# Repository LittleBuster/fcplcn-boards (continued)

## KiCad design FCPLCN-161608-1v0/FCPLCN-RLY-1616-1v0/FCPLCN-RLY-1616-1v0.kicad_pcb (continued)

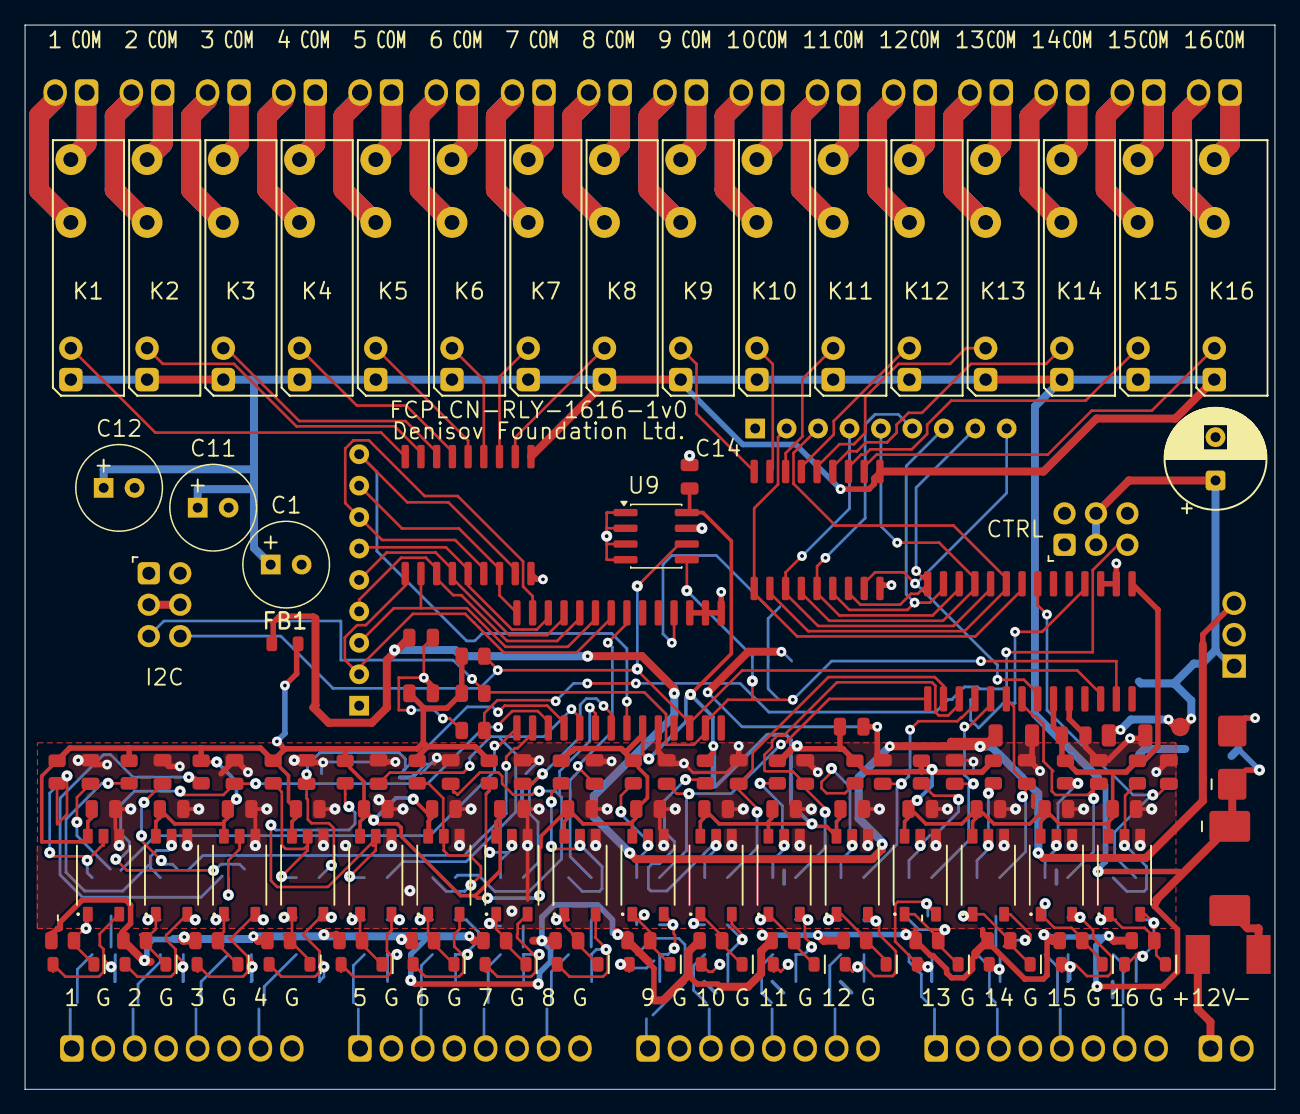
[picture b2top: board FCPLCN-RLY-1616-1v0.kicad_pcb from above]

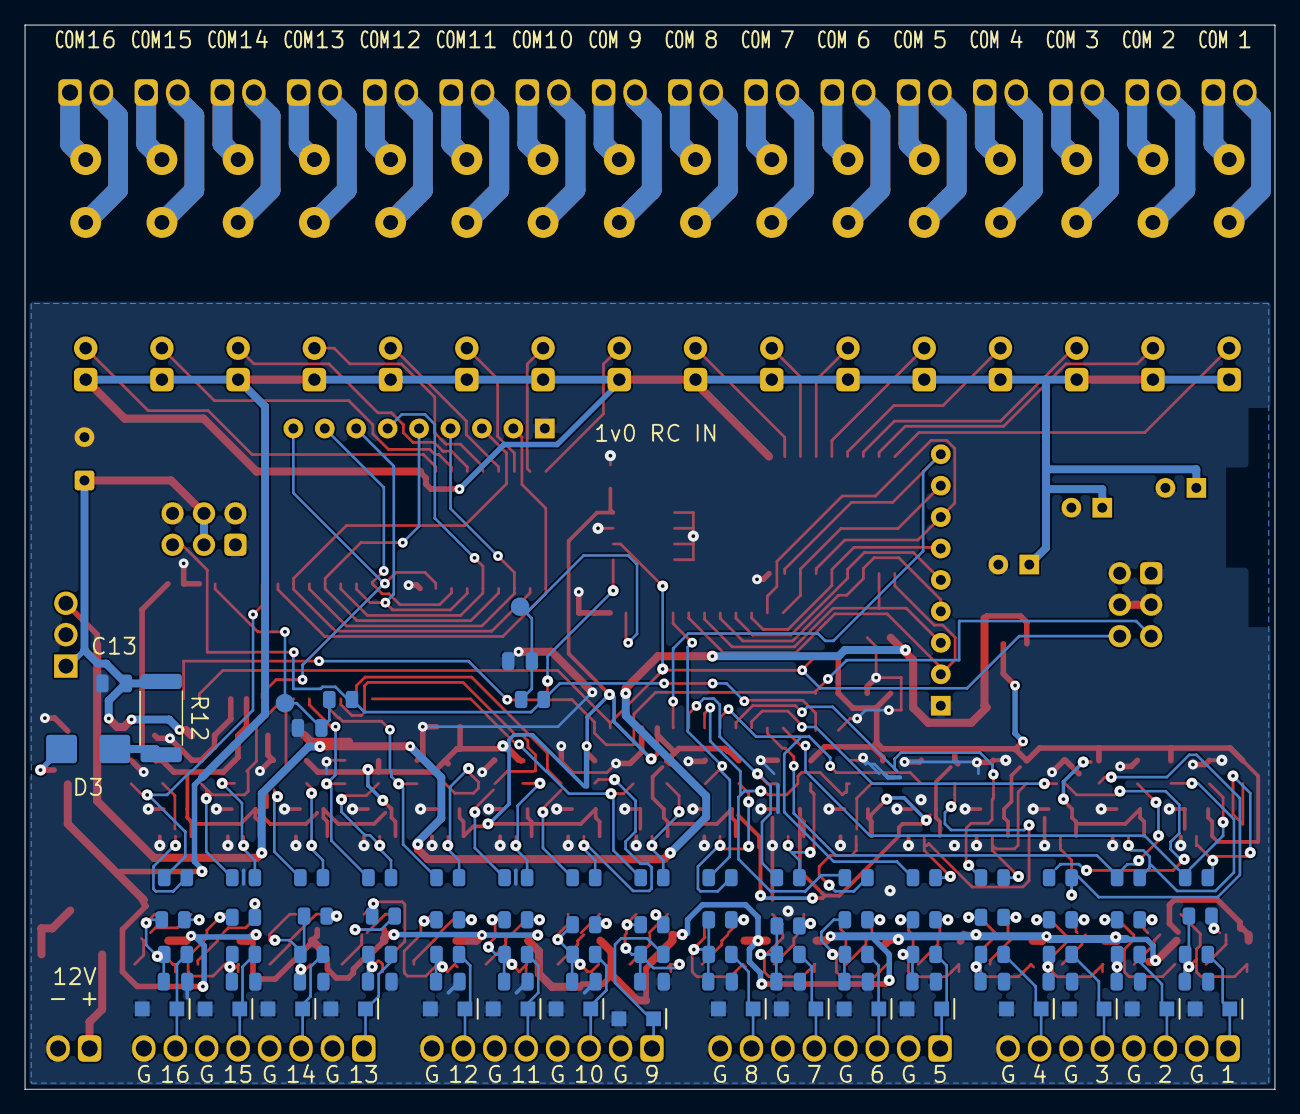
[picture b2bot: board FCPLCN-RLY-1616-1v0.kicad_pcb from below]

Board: 2 copper layers, 101.0 x 86.0 mm, 251 parts (89 on the bottom side), 157 nets.

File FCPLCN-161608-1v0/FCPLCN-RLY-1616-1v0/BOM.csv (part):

refs,value,footprint,qty,datasheet,mpn,manufacturer,tolerance,supplier_part_number,source_url,package,bom_group,power_rating,voltage,dielectric,resistor_type,height_max,cad_footprints
"C1, C11, C12",100u / 35V,RelayBoard:CP_APAQ_ARHA_D6.3mm_P2.5mm_H9max,3,https://www.apaq.com.tw/Templates/att/ARHA_20241121.pdf?lng=en,350ARHA101M06X8P00,APAQ,20%,C217555,https://www.lcsc.com/product-detail/C217555.html,RelayBoard:CP_APAQ_ARHA_D6.3mm_P2.5mm_H9max,,,,,,9 mm,RelayBoard:CP_APAQ_ARHA_D6.3mm_P2.5mm_H9max
"C2, C3",10uF,RelayBoard:C_1206_3216Metric,2,https://product.tdk.com/system/files/dam/doc/product/capacit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,C3216X7R1V106K160AC,TDK,10%,,,1206,C-1206-10uF-35V-X7R-10pct-TDK,,35 V,X7R,,1.8 mm,RelayBoard:C_1206_3216Metric
"C4, C5, C13, C14, C101, C102, C103, C104, C105, C106, C107, C108, C109, C110, C111, C112, C113, C114, C115, C116, C121, C122, C123, C124, C125, C126, C127, C128, C129, C130, C131, C132, C133, C134, C135, C136",100nF,RelayBoard:C_0805_2012Metric,36,,,,10%,,,0805,C-0805-100nF-50V-X7R-10pct,,50 V,X7R,,,RelayBoard:C_0805_2012Metric
"C6, C7",10u / 16V X7R,RelayBoard:C_0805_2012Metric,2,,,,,,,RelayBoard:C_0805_2012Metric,,,,,,,RelayBoard:C_0805_2012Metric
C8,220u / 35V,RelayBoard:CP_Radial_D8.0mm_P3.50mm,1,,,,,,,RelayBoard:CP_Radial_D8.0mm_P3.50mm,,,,,,,RelayBoard:CP_Radial_D8.0mm_P3.50mm
"C9, C10",10nF,RelayBoard:C_0805_2012Metric,2,,,,10%,,,0805,C-0805-10nF-50V-X7R-10pct,,50 V,X7R,,,RelayBoard:C_0805_2012Metric
"C141, C142, C143, C144, C145, C146, C147, C148, C149, C150, C151, C152, C153, C154, C155, C156",1uF,RelayBoard:C_0805_2012Metric,16,https://product.tdk.com/system/files/dam/doc/product/capacit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,C2012X7R1H105K125AB,TDK,10%,,https://product.tdk.com/en/search/capacitor/ceramic/mlcc/inf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,0805,C-0805-1uF-50V-X7R-10pct-TDK,,50 V,X7R,,1.45 mm,RelayBoard:C_0805_2012Metric
D1,SS34-E3,RelayBoard:D_SMC,1,https://www.vishay.com/docs/88751/ss32.pdf,,,,,,RelayBoard:D_SMC,,,,,,,RelayBoard:D_SMC
D2,SMBJ15A,RelayBoard:D_SMB,1,,,,,,,RelayBoard:D_SMB,,,,,,,RelayBoard:D_SMB
D3,B340B-13-F,RelayBoard:D_SMB,1,https://www.diodes.com/datasheet/download/B340B.pdf,,,,,,RelayBoard:D_SMB,,,,,,,RelayBoard:D_SMB
"D101, D102, D103, D104, D105, D106, D107, D108, D109, D110, D111, D112, D113, D114, D115, D116",1N4148W-7-F,RelayBoard:D_SOD-123,16,https://www.diodes.com/datasheet/download/1N4148W.pdf,,,,,,RelayBoard:D_SOD-123,,,,,,,RelayBoard:D_SOD-123
"D121, D122, D123, D124, D125, D126, D127, D128, D129, D130, D131, D132, D133, D134, D135, D136",PTVS15VS1UR,RelayBoard:Nexperia_CFP3_SOD-123W,16,https://assets.nexperia.com/documents/data-sheet/PTVSXS1UR_SER.pdf,,,,,,RelayBoard:Nexperia_CFP3_SOD-123W,,,,,,,RelayBoard:Nexperia_CFP3_SOD-123W
F1,045201.5MRL,RelayBoard:Fuse_Littelfuse-NANO2-451_453,1,https://www.littelfuse.com/assetdocs/littelfuse_fuse_452_454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,045201.5MRL,Littelfuse,,,,RelayBoard:Fuse_Littelfuse-NANO2-451_453,,,,,,,RelayBoard:Fuse_Littelfuse-NANO2-451_453
FB1,220R @100MHz / 2A,RelayBoard:L_0805_PowerFilter,1,https://www.murata.com/en-eu/api/pdfdownloadapi?cate=cgsubCh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,BLM21PG221SN1D,Murata,,,,RelayBoard:L_0805_PowerFilter,,,,,,,RelayBoard:L_0805_PowerFilter
J1,12V IN,RelayBoard:KF128-2.54-2P,1,,,,,,,RelayBoard:KF128-2.54-2P,,,,,,,RelayBoard:KF128-2.54-2P
J2,OUT 1,RelayBoard:KF128-2.54-2P,1,,,,,,,RelayBoard:KF128-2.54-2P,,,,,,,RelayBoard:KF128-2.54-2P
J3,OUT 2,RelayBoard:KF128-2.54-2P,1,,,,,,,RelayBoard:KF128-2.54-2P,,,,,,,RelayBoard:KF128-2.54-2P
J4,OUT 3,RelayBoard:KF128-2.54-2P,1,,,,,,,RelayBoard:KF128-2.54-2P,,,,,,,RelayBoard:KF128-2.54-2P
J5,OUT 4,RelayBoard:KF128-2.54-2P,1,,,,,,,RelayBoard:KF128-2.54-2P,,,,,,,RelayBoard:KF128-2.54-2P
J6,OUT 5,RelayBoard:KF128-2.54-2P,1,,,,,,,RelayBoard:KF128-2.54-2P,,,,,,,RelayBoard:KF128-2.54-2P
J7,OUT 6,RelayBoard:KF128-2.54-2P,1,,,,,,,RelayBoard:KF128-2.54-2P,,,,,,,RelayBoard:KF128-2.54-2P
J8,OUT 7,RelayBoard:KF128-2.54-2P,1,,,,,,,RelayBoard:KF128-2.54-2P,,,,,,,RelayBoard:KF128-2.54-2P
J9,OUT 8,RelayBoard:KF128-2.54-2P,1,,,,,,,RelayBoard:KF128-2.54-2P,,,,,,,RelayBoard:KF128-2.54-2P
J10,OUT 9,RelayBoard:KF128-2.54-2P,1,,,,,,,RelayBoard:KF128-2.54-2P,,,,,,,RelayBoard:KF128-2.54-2P
J11,OUT 10,RelayBoard:KF128-2.54-2P,1,,,,,,,RelayBoard:KF128-2.54-2P,,,,,,,RelayBoard:KF128-2.54-2P
J12,OUT 11,RelayBoard:KF128-2.54-2P,1,,,,,,,RelayBoard:KF128-2.54-2P,,,,,,,RelayBoard:KF128-2.54-2P
J13,OUT 12,RelayBoard:KF128-2.54-2P,1,,,,,,,RelayBoard:KF128-2.54-2P,,,,,,,RelayBoard:KF128-2.54-2P
J14,OUT 13,RelayBoard:KF128-2.54-2P,1,,,,,,,RelayBoard:KF128-2.54-2P,,,,,,,RelayBoard:KF128-2.54-2P
J15,OUT 14,RelayBoard:KF128-2.54-2P,1,,,,,,,RelayBoard:KF128-2.54-2P,,,,,,,RelayBoard:KF128-2.54-2P
J16,OUT 15,RelayBoard:KF128-2.54-2P,1,,,,,,,RelayBoard:KF128-2.54-2P,,,,,,,RelayBoard:KF128-2.54-2P
J17,OUT 16,RelayBoard:KF128-2.54-2P,1,,,,,,,RelayBoard:KF128-2.54-2P,,,,,,,RelayBoard:KF128-2.54-2P
J21,IN 1–4,RelayBoard:KF128-2.54-8P,1,https://www.kefaelectronic.com/KF128-2-54-PCB-Terminal-Block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,,,,,,RelayBoard:KF128-2.54-8P,,,,,,,RelayBoard:KF128-2.54-8P
J25,IN 5–8,RelayBoard:KF128-2.54-8P,1,https://www.kefaelectronic.com/KF128-2-54-PCB-Terminal-Block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,,,,,,RelayBoard:KF128-2.54-8P,,,,,,,RelayBoard:KF128-2.54-8P
J29,IN 9–12,RelayBoard:KF128-2.54-8P,1,https://www.kefaelectronic.com/KF128-2-54-PCB-Terminal-Block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,,,,,,RelayBoard:KF128-2.54-8P,,,,,,,RelayBoard:KF128-2.54-8P
J33,IN 13–16,RelayBoard:KF128-2.54-8P,1,https://www.kefaelectronic.com/KF128-2-54-PCB-Terminal-Block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,,,,,,RelayBoard:KF128-2.54-8P,,,,,,,RelayBoard:KF128-2.54-8P
J43,STACK I²C,RelayBoard:StackSocket_2x03_P2.54mm,1,https://suddendocs.samtec.com/prints/ssw-1xx-xx-xxx-x-xx-xxx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,SSW-103-01-L-D,Samtec,,,,RelayBoard:StackSocket_2x03_P2.54mm,,,,,,,RelayBoard:StackSocket_2x03_P2.54mm
J44,STACK CTRL,RelayBoard:StackSocket_2x03_P2.54mm,1,https://suddendocs.samtec.com/prints/ssw-1xx-xx-xxx-x-xx-xxx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,SSW-103-01-L-D,Samtec,,,,RelayBoard:StackSocket_2x03_P2.54mm,,,,,,,RelayBoard:StackSocket_2x03_P2.54mm
"K1, K2, K3, K4, K5, K6, K7, K8, K9, K10, K11, K12, K13, K14, K15, K16",HF49FD/012-1H11,RelayBoard:Relay_SPST_Hongfa_HF49FD-1H11,16,https://www.hongfa.com/product/industrial-relay/HF49FD,,,,,,RelayBoard:Relay_SPST_Hongfa_HF49FD-1H11,,,,,,,RelayBoard:Relay_SPST_Hongfa_HF49FD-1H11
"R2, R3, R181, R182, R183, R184, R185, R186, R187, R188, R189, R190, R191, R192, R193, R194, R195, R196",4.7k,RelayBoard:R_0805_2012Metric,18,,,,1%,,,0805,R-0805-4.7k-1pct-125mW,0.125 W,,,,,RelayBoard:R_0805_2012Metric
"R4, R121, R122, R123, R124, R125, R126, R127, R128, R129, R130, R131, R132, R133, R134, R135, R136",10k,RelayBoard:R_0805_2012Metric,17,,,,1%,,,0805,R-0805-10k-1pct-125mW,0.125 W,,,,,RelayBoard:R_0805_2012Metric
"R10, R11, R141, R142, R143, R144, R145, R146, R147, R148, R149, R150, R151, R152, R153, R154, R155, R156",470R,RelayBoard:R_0805_2012Metric,18,,,,1%,,,0805,R-0805-470R-1pct-125mW,0.125 W,,,,,RelayBoard:R_0805_2012Metric
R12,1R / 2W pulse,RelayBoard:R_2512_6332Metric,1,https://www.bourns.com/docs/product-datasheets/crm.pdf,CRM2512-FX-1R00ELF,Bourns,1%,,,RelayBoard:R_2512_6332Metric,,2 W,,,,,RelayBoard:R_2512_6332Metric
"R101, R102, R103, R104, R105, R106, R107, R108, R109, R110, R111, R112, R113, R114, R115, R116",1.2k,RelayBoard:R_0805_Wetting,16,https://www.vishay.com/docs/20115/crcwhp.pdf,CRCW08051K20FKTAHP,Vishay,1%,,,0805,R-0805-1.2k-1pct-500mW-Vishay-HP,0.5 W,,,,,RelayBoard:R_0805_Wetting
"R161, R162, R163, R164, R165, R166, R167, R168, R169, R170, R171, R172, R173, R174, R175, R176",220R,RelayBoard:R_0805_2012Metric,16,https://www.vishay.com/docs/20115/crcwhp.pdf,CRCW0805220RFKTAHP,Vishay,1%,,,0805,R-0805-220R-1pct-500mW-Vishay-HP,0.5 W,,,,,RelayBoard:R_0805_2012Metric
"RN1, RN2",8 × 10k,RelayBoard:R_Array_SIP9,2,https://www.bourns.com/data/global/pdfs/4600X.pdf,,,,,,RelayBoard:R_Array_SIP9,,,,,,,RelayBoard:R_Array_SIP9
U2,R-78K3.3-0.5,RelayBoard:RECOM_R-78K3.3-0.5_SIP3_P2.54mm,1,https://recom-power.com/pdf/Innoline/R-78K-0.5.pdf,R-78K3.3-0.5,RECOM,,,,RelayBoard:RECOM_R-78K3.3-0.5_SIP3_P2.54mm,,,,,,,RelayBoard:RECOM_R-78K3.3-0.5_SIP3_P2.54mm
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
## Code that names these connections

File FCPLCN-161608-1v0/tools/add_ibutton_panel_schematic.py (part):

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
def migrate_gpio43(path, original):
    """Use the available UART0 TX pin for the indicator; preserve GPIO3 as NC."""
    if '(label "IB_LED_CPU" (at 91.44 81.28' in original:
        return
    for prefix in ('(wire (pts (xy 50.8 62.23) (xy 45.72 62.23))',
                   '(label "IB_LED_CPU" (at 45.72 62.23'):
        start=original.index(prefix)
        end=expression_end(original,start)
        original=original[:start]+original[end:]
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    s=Schematic(path.stem,namespace='RelayStack',uuid_seed='FCPLCn/iButton-GPIO43-v1')
    s.root='"'+re.search(r'\(uuid "([^\"]+)"\)',original).group(1)+'"'
    s.wire((86.36,81.28),(91.44,81.28))
    s.label('IB_LED_CPU',(91.44,81.28),angle=0,size=1.03)
    old_nc='(no_connect (at 50.8 62.23) (uuid "6232113c-bb1f-588d-852d-27e3b12f0878"))'
    original=original.rstrip()[:-1]+'\n'+old_nc+'\n'+'\n'.join(s.elements)+'\n)\n'
    original=original.replace('GPIO3 LED / GPIO45 BUZZER: HIGH = ON; 10k pull-downs ensure LOW on reset. Default eFuses required.',
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def migrate_driver_channels(path):
    """Use adjacent channels 7/6 near the terminal, preserving the circuit."""
    original = path.read_text()
    if '(label "IB_LED_BASE" (at 304.8 693.42' in original:
        assert '(label "IB_BUZZ_BASE" (at 304.8 690.88' in original
        return
    for before, after in [
        ('(label "IB_LED_BASE" (at 304.8 678.18', '(label "GND" (at 304.8 678.18'),
        ('(label "IB_BUZZ_BASE" (at 304.8 680.72', '(label "GND" (at 304.8 680.72'),
        ('(label "GND" (at 304.8 690.88', '(label "IB_BUZZ_BASE" (at 304.8 690.88'),
        ('(label "GND" (at 304.8 693.42', '(label "IB_LED_BASE" (at 304.8 693.42'),
    ]:
        assert original.count(before) == 1, before
        original = original.replace(before, after)
    for prefix in (
        '(no_connect (at 347.98 693.42)', '(no_connect (at 347.98 690.88)',
        '(wire (pts (xy 347.98 680.72) (xy 355.6 680.72))',
        '(label "IB_BUZZ_OUT" (at 355.6 680.72',
        '(wire (pts (xy 347.98 678.18) (xy 355.6 678.18))',
        '(label "IB_LED_SINK" (at 355.6 678.18',
    ):
        start = original.index(prefix)
        end = expression_end(original, start)
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def migrate_buzzer_pulldown(path):
    """Pull down the buzzer base; the CPU sees 680R + 10k at reset."""
    text = path.read_text()
    before = '(label "IB_BUZZ_CPU" (at 163.83 688.34'
    after = '(label "IB_BUZZ_BASE" (at 163.83 688.34'
    if before not in text:
        assert after in text
        return
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
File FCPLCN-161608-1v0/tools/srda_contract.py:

"""SRDA pin/net/part contract. Read-only; no KiCad dependency."""
SRDA_REFS = ('D1', 'D2', 'D3', 'D4', 'D6')
SRDA_DATASHEET = "https://www.littelfuse.com/assetdocs/tvs-diode-array-spa-srda05-datasheet?assetguid=5e6854f4-4140-4034-b7b2-d3793470da22"
SERIES_MPN = 'CRCW0805100RFKTAHP'
SERIES_DATASHEET = 'https://www.vishay.com/docs/20115/crcwhp.pdf'
ARRAYS = {
 'D1': ('GND', 'TVS_USB_REF', [None,None,'USB_DN','USB_DP']),
 'D2': ('GND_ISO', 'TVS_DATA14_REF_ISO', ['DATA1_ISO','DATA2_ISO','DATA3_ISO','DATA4_ISO']),
 'D3': ('GND_ISO', 'TVS_I2C_REF_ISO', ['SDA_ISO','SCL_ISO',None,None]),
 'D4': ('GND', 'TVS_LED_REF', ['LED_NET_OUT','LED_STATUS_OUT','LED_ALARM_OUT','LED_PWR_OUT']),
 'D6': ('GND_ISO', 'TVS_DATA58_REF_ISO', ['DATA5_ISO','DATA6_ISO','DATA7_ISO','DATA8_ISO'])}

def expected_arrays():
 out = {}
 for ref,(ground,ref1,signals) in ARRAYS.items():
  out[ref] = {'2':ref1,'3':ref1,'5':ground,'8':ground}
  for idx,(pin,signal) in enumerate(zip(('1','4','6','7'),signals),1):
   out[ref][pin] = signal or ground
 return out

def check_srda_contract(refs, nets, value, field, footprint, *, inventory_count=148):
 errors=[]
 raw_field=field
 def field(ref,key):
  try:return raw_field(ref,key)
  except KeyError:return ""
 def check(ok,message):
  if not ok: errors.append(message)
 check(len(refs)==inventory_count,f'Upper inventory must contain {inventory_count} components')
 check(not any(r in refs for r in ('D5','D7','D10')),'Obsolete PESD references D5/D7/D10 remain')
 check(not any('PESD' in value(r).upper() or 'PESD' in field(r,'MPN').upper() for r in refs),'PESD part remains')
 for ref,expected in expected_arrays().items():
  if ref not in refs: errors.append('Missing SRDA '+ref);continue
  check(nets(ref)==expected,ref+' SRDA pin-net map differs')
  check(value(ref)==field(ref,'MPN')=='SRDA05-4BTG',ref+' exact SRDA MPN differs')
  check(field(ref,'Manufacturer')=='Littelfuse',ref+' manufacturer differs')
  check(footprint(ref)==('RelayStack:SOIC8_SRDA_USB_Clearance' if ref=='D1' else 'Package_SO:SOIC-8_3.9x4.9mm_P1.27mm'),ref+' approved SOIC8 footprint differs')
  check(field(ref,'Datasheet')==SRDA_DATASHEET,ref+' datasheet differs')
  positive=expected['2']
  pins={(r,p) for r in refs for p,n in nets(r).items() if n==positive}
  check(pins=={(ref,'2'),(ref,'3')},ref+' REF1 is not an exclusive floating two-pin node')
  for p,n in expected.items():
   if n.startswith('unconnected-'):
    check({(r,q) for r in refs for q,k in nets(r).items() if k==n}=={(ref,p)},ref+'.'+p+' unused IO is not isolated')
 for i in range(10):
  ref='R'+str(61+i);name='DATA'+str(i+1) if i<8 else ('SDA','SCL')[i-8]
  if ref not in refs: errors.append('Missing FIELD series '+ref);continue
  check(nets(ref)=={'1':name+'_ISO','2':name+'_IC_ISO'},ref+' FIELD series pin-net map differs')
  check(value(ref)=='100R' and field(ref,'Tolerance')=='1%',ref+' value/tolerance differs')
  check(field(ref,'MPN')==SERIES_MPN and field(ref,'Manufacturer')=='Vishay',ref+' pulse-rated MPN differs')
  check(footprint(ref)=='Resistor_SMD:R_0805_2012Metric',ref+' 0805 footprint differs')
  check(field(ref,'Datasheet')==SERIES_DATASHEET,ref+' datasheet differs')
 for ref,a,b in [('U6',1,2),('U8',3,4),('U9',5,6),('U15',7,8)]:
  check(nets(ref)=={'1':'+3V3','2':f'DATA{a}_CPU','3':f'DATA{b}_CPU','4':'GND','5':'GND_ISO','6':f'DATA{b}_IC_ISO','7':f'DATA{a}_IC_ISO','8':'+5V_ISO'},ref+' isolated DATA pin map differs')
 check(nets('U7')=={'1':'+3V3','2':'ISO_SDA_CPU','3':'ISO_SCL_CPU','4':'GND','5':'GND_ISO','6':'SCL_IC_ISO','7':'SDA_IC_ISO','8':'+3V3_ISO'},'U7 isolated I2C pin map differs')
 for i,ref in enumerate(('R17','R18','R35','R36','R39','R40','R59','R60'),1):
  check(nets(ref)=={'1':'+5V_ISO','2':f'DATA{i}_IC_ISO'},ref+' pullup must be on IC side of series resistor')
 for ref,name in [('R21','SDA'),('R22','SCL')]:
  check(nets(ref)=={'1':'+3V3_ISO','2':name+'_IC_ISO'},ref+' I2C pullup must be on IC side')
 for ref,name in [('R11','USB_DN'),('R12','USB_DP')]:
  check(nets(ref)=={'1':name,'2':name+'_CPU'} and value(ref) in ('22','22R'),ref+' existing USB22R must remain')
 return errors

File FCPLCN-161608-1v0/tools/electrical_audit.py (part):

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 require(nets(ref)==pins,ref+' physical pin-net mapping mismatch')
 if ref in expected_values:require(fp[ref].GetValue()==expected_values[ref],ref+' value mismatch')
for ref in ['R47','R48','R49','R50','R51','R52','R54','R55','R56']:require(field(ref,'Tolerance')=='1%',ref+' requires1%')
for pin,net in [('12','RS485_TX_CPU'),('24','RS485_RX_CPU'),('25','RS485_DIR_CPU')]:require(nets('U1')[pin]==net,'ESP32S3 module pin'+pin+' wrong signal')
mpns={'U11':('ADM2687EBRIZ','Analog Devices'),'U12':('R-78K3.3-0.5','RECOM'),'U13':('74LVC125AD,118','Nexperia'),'U14':('74LVC125AD,118','Nexperia'),'FB1':('BLM21PG221SN1D','Murata'),'D9':('CDSOT23-SM712','Bourns'),'C37':('C3216X5R1V226M160AC','TDK'),'C38':('C3216X7R1E106K160AB','TDK')}
mpns['C38']=(TDK_10UF_MPN,'TDK')
for ref,(mpn,manufacturer) in mpns.items():
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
